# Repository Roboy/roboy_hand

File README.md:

Flashing with SWD via raspberry pi with openocd 

##  Default RPI-2 B settings
ip: 192.168.0.106

user: pi
pw: Roboy2016

##  access RPI
ssh pi@192.168.0.106

# working dir:
cd ~/Projekts/openocd/testing/samd21/

At91samd was programmed via openocd with an raspberry pi (https://iosoft.blog/2019/01/28/raspberry-pi-openocd/)

config file 

##  Pin header chestNut-PCB
1	VCC +3.3V
2	SWDIO
3	SWCLK
4	NC/
5	RESET
6	GND

##master config
source rpi2.cfg

transport select swd
adapter_khz 1000

set CHIPNAME at91samd21g18
source [find target/at91samdXX.cfg]

bindto 0.0.0.0

##raspberry config
# rpi2.cfg: OpenOCD interface on RPi v2+
echo "rpi2 cfg"
# Use RPi GPIO pins
interface bcm2835gpio

# Base address of I/O port
bcm2835gpio_peripheral_base 0x3F000000

# Clock scaling
bcm2835gpio_speed_coeffs 146203 36

# SWD                swclk swdio
# Header pin numbers 22    18
bcm2835gpio_swd_nums 25    24

# JTAG                tck tms tdi tdo
# Header pin numbers  22  18  16  15 
bcm2835gpio_jtag_nums 25  24  23  22

bcm2835gpio_srst_num 18
reset_config srst_only srst_push_pull

##rpi commands
###start openocd server
sudo openocd -f samd21_test.cfg
###telnet
telnet localhost 4444
###telnet commands
init
targets
reset halt
at91samd chip-erase
reset halt
at91samd bootloader 0
#program /home/pi/Projekts/openocd/testing/samd21/samd21_mkr1000.bin verify
#program /home/pi/Projekts/openocd/testing/samd21/samd21_sam_ba.bin verify
#program /home/pi/Projekts/openocd/testing/samd21/zero/samd21_sam_ba.bin verify
program /home/pi/Projekts/openocd/testing/samd21/samd21_genu_mkr1000.bin verify

at91samd bootloader 8192
reset
shutdown

#then mk1000 can be seltected in arduino after init flash the board will apear as "arduino zero"

Arduino head changes
Changed Pins.ino for finger.h file 

finger[0].attach(10, 11, A1, A9, false); // attach the thumb
finger[3].attach(4, 3, A0, 1, false); // attach the ring & pinky (fingers are inverted)
finger[1].attach(9, 6, A3, 0, false); // attach the index (finger is inverted)
finger[2].attach(5, 12, A2, A5, false); //doesn't move (could be wronge pin

#dump deltet ...... :
interface cmsis-dap
transport select swd
#Target
set CHIPNAME at91samd21e18
source [find target/at91samdXX2.cfg]
#source [find target/stm32f1x.cfg]

init
targets
reset halt
at91samd chip-erase
reset halt
at91samd bootloader 0
program D:/projects/SAMD_Loader/Firmware/all.bin verify
at91samd bootloader 8192
reset
shutdown

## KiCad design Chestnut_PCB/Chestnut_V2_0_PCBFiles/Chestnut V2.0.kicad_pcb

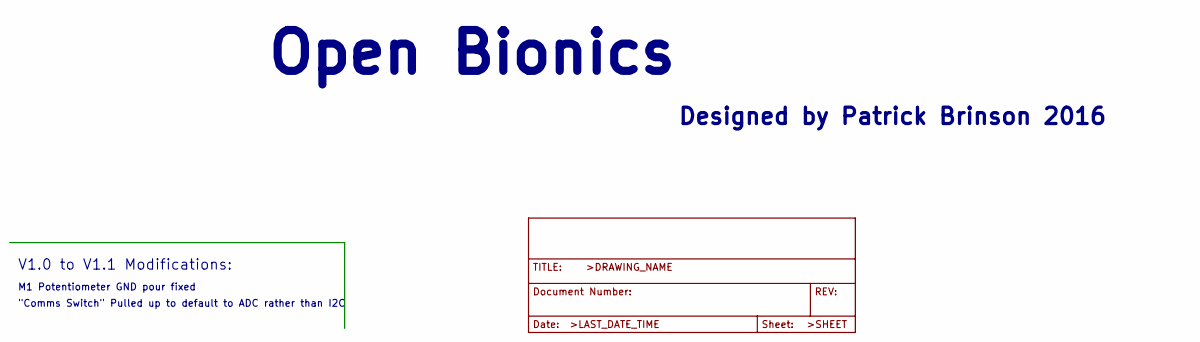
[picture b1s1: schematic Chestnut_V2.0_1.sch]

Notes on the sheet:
Open Bionics
Designed by Patrick Brinson 2016
V1.0 to V1.1 Modifications:
M1 Potentiometer GND pour fixed
"Comms Switch" Pulled up to default to ADC rather than I2C

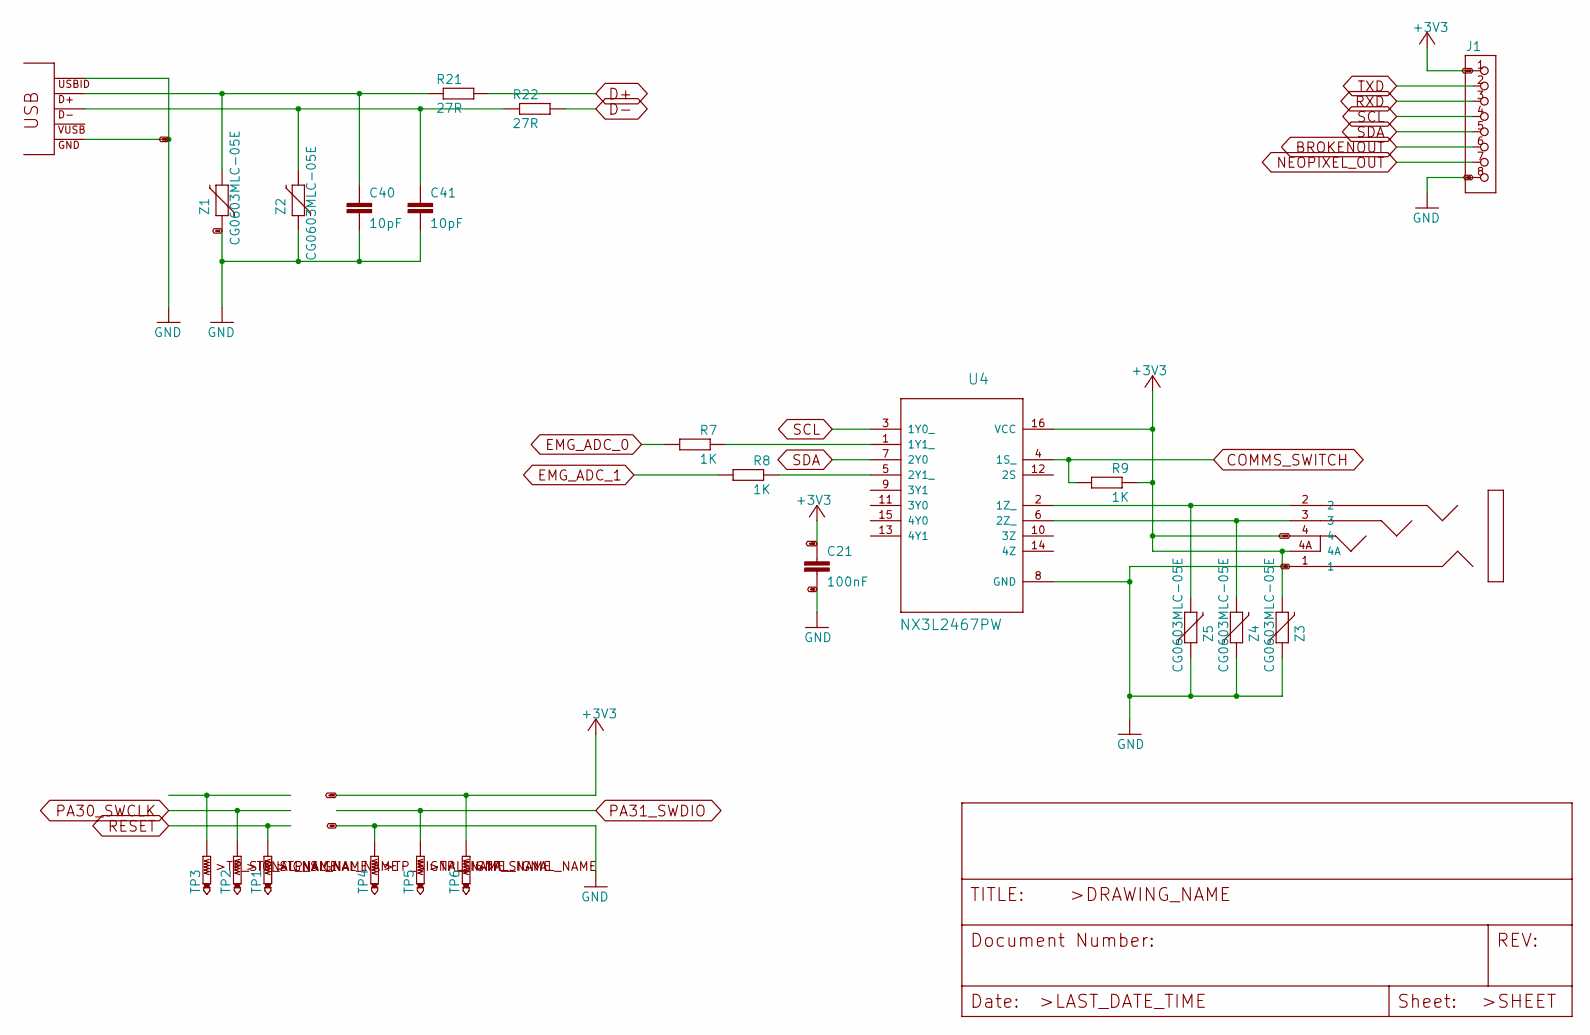
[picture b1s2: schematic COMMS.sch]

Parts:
C21: 100nF; C0402
C40, C41: 10pF; C0402
J1: CON_HEADER_1X08-PTH; M1X8
R7, R8, R9: 1K; R0402
R21, R22: 27R; R0402
TP1, TP2, TP3, TP4, TP5, TP6: PTR1TP11R; TP11R
U4: NX3L2467PW; SOP65P640X110-16N
U$7: LUMBERG_1503-13-VP3
USB1: CON-USB-F-MICRO-B; CONN_USB_MICRO-B
Z1, Z2, Z3, Z4, Z5: CG0603MLC-05E; CT_CN0603

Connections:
+3V3: C21.1, J1.1, R9.1, TP6.TP, U4.16 (VCC), U$7.4, U$7.4A, Z3.2; also elsewhere on the board
BROKENOUT: J1.6; also elsewhere on the board
COMMS_SWITCH: R9.2, U4.4 (1S_); also elsewhere on the board
D+: R21.2; also elsewhere on the board
D-: R22.2; also elsewhere on the board
EMG_ADC_0: R7.2; also elsewhere on the board
EMG_ADC_1: R8.2; also elsewhere on the board
GND: C21.2, C40.2, C41.2, J1.8, TP4.TP, U4.8 (GND), U$7.1, USB1.P4 (USBID), USB1.P5 (GND), Z1.1, Z2.1, Z3.1, Z4.1, Z5.1; also elsewhere on the board
NEOPIXEL_OUT: J1.7; also elsewhere on the board
unnamed: C40.1, R21.1, USB1.P3 (D+), Z1.2
unnamed: C41.1, R22.1, USB1.P2 (D-), Z2.2
unnamed: R7.1, U4.1 (1Y1_)
unnamed: R8.1, U4.5 (2Y1_)
unnamed: U4.2 (1Z_), U$7.2, Z5.2
unnamed: U4.6 (2Z_), U$7.3, Z4.2
PA30_SWCLK: TP2.TP; also elsewhere on the board
PA31_SWDIO: TP5.TP; also elsewhere on the board
RESET: TP1.TP; also elsewhere on the board
RXD: J1.3; also elsewhere on the board
SCL: J1.4, U4.3 (1Y0_); also elsewhere on the board
SDA: J1.5, U4.7 (2Y0); also elsewhere on the board
TXD: J1.2; also elsewhere on the board

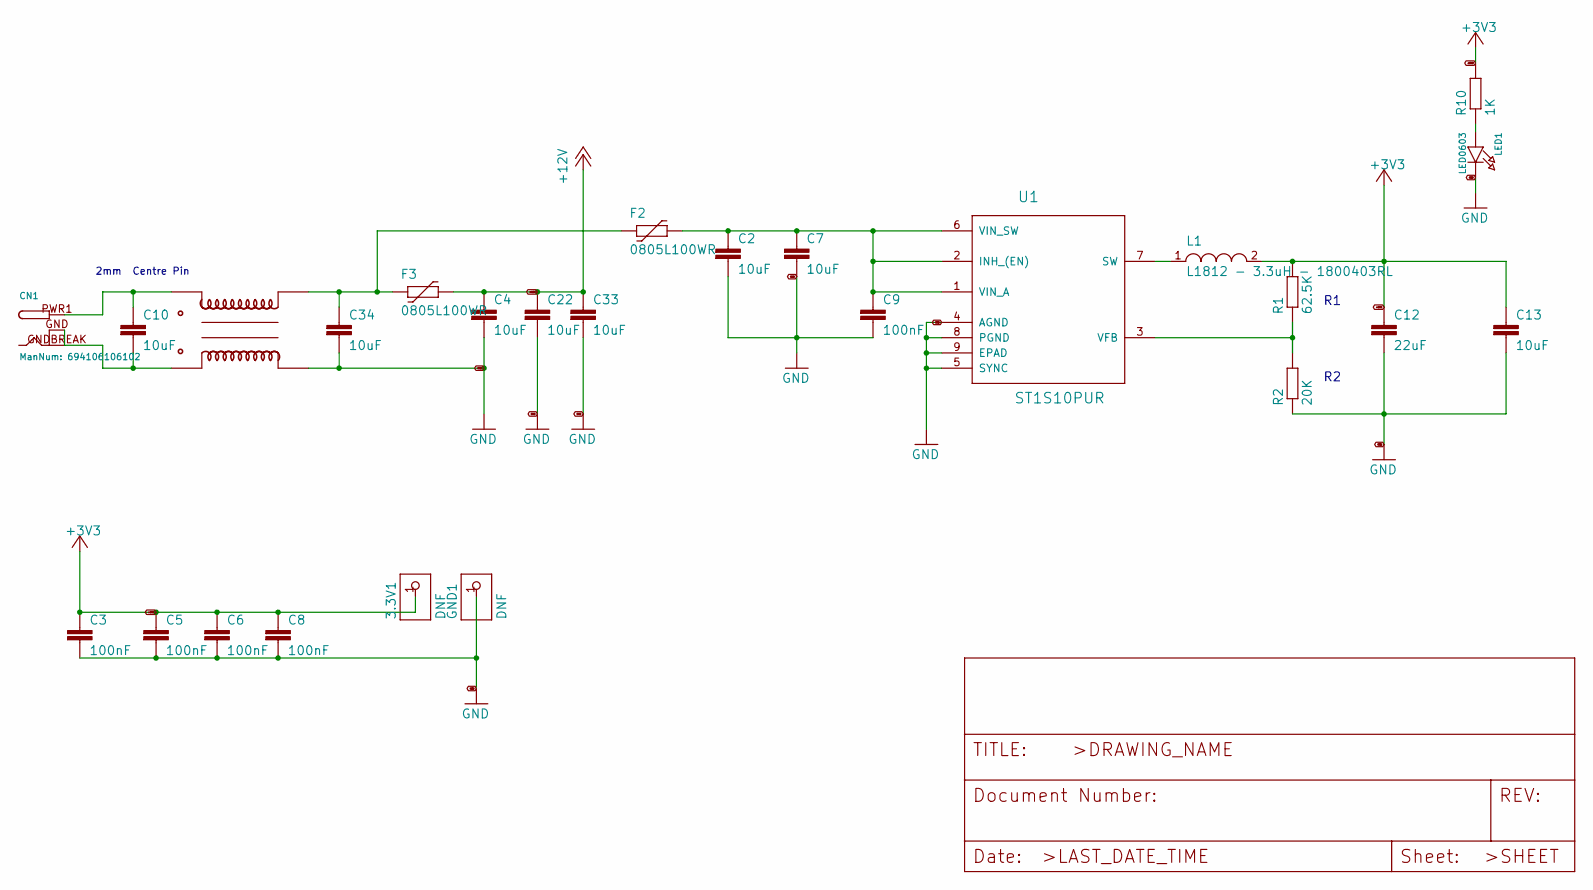
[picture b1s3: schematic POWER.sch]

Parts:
3.3V: DNF; 1X01_ROUND
C2, C4, C7, C10, C13, C22, C33, C34: 10uF; C0805
C3, C5, C6, C8, C9: 100nF; C0402
C12: 22uF; C1210
CN1: ManNum: 694106106102; DCJACK_2MM_SMT
F2, F3: 0805L100WR; PTC0805
GND: DNF; 1X01_ROUND
L1: L1812 - 3.3uH - 1800403RL; L1812
LED1: LED0603; CHIPLED_0603
R1: 62.5K; R0603
R2: 20K; R0603
R10: 1K; R0402
U1: ST1S10PUR; DFN400X400X100-9N
U$5: DLW5BTN501SQ2L

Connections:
+3V3: C3.1, C5.1, C6.1, C8.1, C12.1, C13.1, L1.2, R1.2, R10.2; also elsewhere on the board
+12V: C4.1, C22.1, C33.1, F3.2; also elsewhere on the board
GND: C2.2, C3.2, C4.2, C5.2, C6.2, C7.2, C8.2, C9.2, C12.2, C13.2, C22.2, C33.2, C34.2, LED1.C, R2.1, U1.4 (AGND), U1.5 (SYNC), U1.8 (PGND), U1.9 (EPAD), U$5.4; also elsewhere on the board
unnamed: C2.1, C7.1, C9.1, F2.2, U1.1 (VIN_A), U1.2 (INH_(EN)), U1.6 (VIN_SW)
unnamed: C10.1, CN1.PWR1 (PWR), U$5.1
unnamed: C10.2, CN1.GND (GNDBREAK), CN1.GNDBREAK (GND), U$5.3
unnamed: C34.1, F2.1, F3.1, U$5.2
unnamed: L1.1, U1.7 (SW)
unnamed: LED1.A, R10.1
unnamed: R1.1, R2.2, U1.3 (VFB)

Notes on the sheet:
2mm Centre Pin

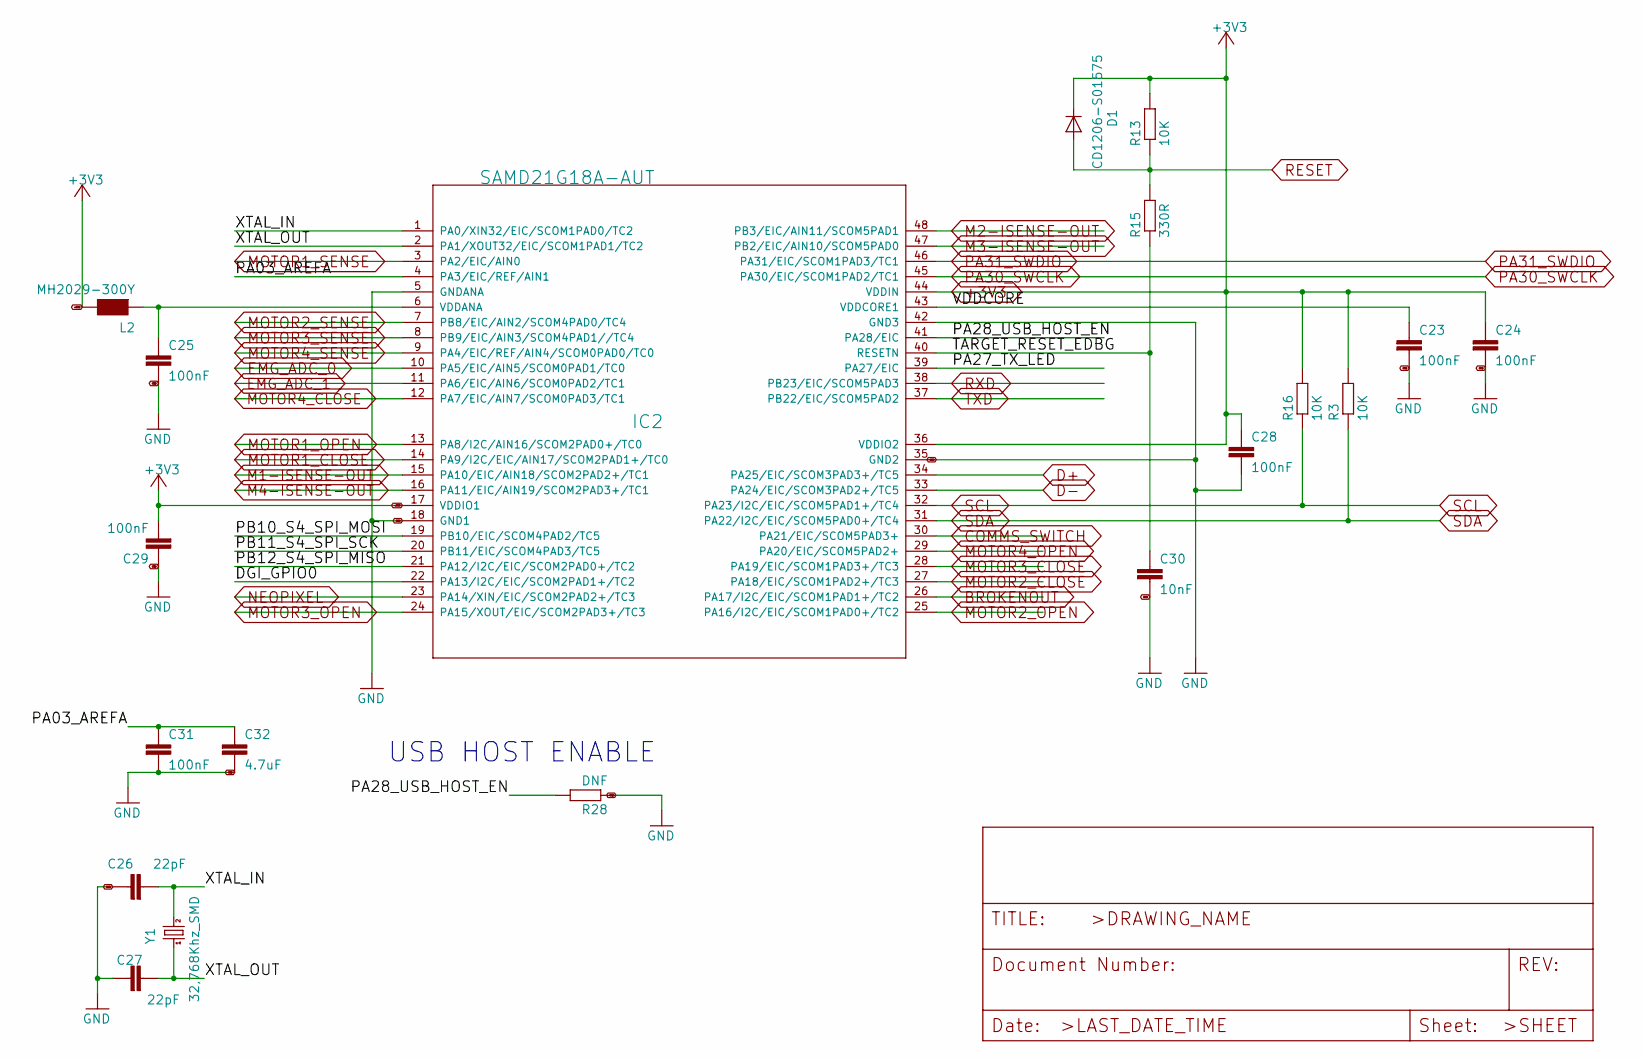
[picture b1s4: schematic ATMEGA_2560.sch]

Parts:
C23, C24, C25, C28, C29, C31: 100nF; C0402
C26, C27: 22pF; C0402
C30: 10nF; C0402
C32: 4.7uF; C0603
D1: CD1206-S01575; MINIMELF
IC2: SAMD21G18A-AUT; INTEGRATEDCIRCUITS_TQFP48-7X7
L2: MH2029-300Y; 0805
R3, R13, R16: 10K; R0402
R15: 330R; R0402
R28: DNF; R0402
Y1: 32,768Khz_SMD; RESONATOR_EPSON_FC_145

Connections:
+3V3: C24.1, C28.1, C29.2, D1.C, IC2.17 (VDDIO1), IC2.36 (VDDIO2), IC2.44 (VDDIN), L2.2, R3.2, R13.2, R16.2; also elsewhere on the board
/ATMEGA 2560/DGI_GPIO0: IC2.22 (PA13/I2C/EIC/SCOM2PAD1+/TC2)
/ATMEGA 2560/PA03_AREFA: C31.1, C32.1, IC2.4 (PA3/EIC/REF/AIN1)
/ATMEGA 2560/PA27_TX_LED: IC2.39 (PA27/EIC)
/ATMEGA 2560/PA28_USB_HOST_EN: IC2.41 (PA28/EIC), R28.2
/ATMEGA 2560/PB10_S4_SPI_MOSI: IC2.19 (PB10/EIC/SCOM4PAD2/TC5)
/ATMEGA 2560/PB11_S4_SPI_SCK: IC2.20 (PB11/EIC/SCOM4PAD3/TC5)
/ATMEGA 2560/PB12_S4_SPI_MISO: IC2.21 (PA12/I2C/EIC/SCOM2PAD0+/TC2)
/ATMEGA 2560/TARGET_RESET_EDBG: C30.1, IC2.40 (RESETN), R15.1
/ATMEGA 2560/VDDCORE: C23.1, IC2.43 (VDDCORE1)
/ATMEGA 2560/XTAL_IN: C26.2, IC2.1 (PA0/XIN32/EIC/SCOM1PAD0/TC2), Y1.P$2 (2)
/ATMEGA 2560/XTAL_OUT: C27.2, IC2.2 (PA1/XOUT32/EIC/SCOM1PAD1/TC2), Y1.P$1 (1)
BROKENOUT: IC2.26 (PA17/I2C/EIC/SCOM1PAD1+/TC2); also elsewhere on the board
COMMS_SWITCH: IC2.30 (PA21/EIC/SCOM5PAD3+); also elsewhere on the board
D+: IC2.34 (PA25/EIC/SCOM3PAD3+/TC5); also elsewhere on the board
D-: IC2.33 (PA24/EIC/SCOM3PAD2+/TC5); also elsewhere on the board
EMG_ADC_0: IC2.10 (PA5/EIC/AIN5/SCOM0PAD1/TC0); also elsewhere on the board
EMG_ADC_1: IC2.11 (PA6/EIC/AIN6/SCOM0PAD2/TC1); also elsewhere on the board
GND: C23.2, C24.2, C25.2, C26.1, C27.1, C28.2, C29.1, C30.2, C31.2, C32.2, IC2.5 (GNDANA), IC2.18 (GND1), IC2.35 (GND2), IC2.42 (GND3), R28.1; also elsewhere on the board
M1-ISENSE-OUT: IC2.15 (PA10/EIC/AIN18/SCOM2PAD2+/TC1); also elsewhere on the board
M2-ISENSE-OUT: IC2.48 (PB3/EIC/AIN11/SCOM5PAD1); also elsewhere on the board
M3-ISENSE-OUT: IC2.47 (PB2/EIC/AIN10/SCOM5PAD0); also elsewhere on the board
M4-ISENSE-OUT: IC2.16 (PA11/EIC/AIN19/SCOM2PAD3+/TC1); also elsewhere on the board
MOTOR1_CLOSE: IC2.14 (PA9/I2C/EIC/AIN17/SCOM2PAD1+/TC0); also elsewhere on the board
MOTOR1_OPEN: IC2.13 (PA8/I2C/AIN16/SCOM2PAD0+/TC0); also elsewhere on the board
MOTOR1_SENSE: IC2.3 (PA2/EIC/AIN0); also elsewhere on the board
MOTOR2_CLOSE: IC2.27 (PA18/EIC/SCOM1PAD2+/TC3); also elsewhere on the board
MOTOR2_OPEN: IC2.25 (PA16/I2C/EIC/SCOM1PAD0+/TC2); also elsewhere on the board
MOTOR2_SENSE: IC2.7 (PB8/EIC/AIN2/SCOM4PAD0/TC4); also elsewhere on the board
MOTOR3_CLOSE: IC2.28 (PA19/EIC/SCOM1PAD3+/TC3); also elsewhere on the board
MOTOR3_OPEN: IC2.24 (PA15/XOUT/EIC/SCOM2PAD3+/TC3); also elsewhere on the board
MOTOR3_SENSE: IC2.8 (PB9/EIC/AIN3/SCOM4PAD1//TC4); also elsewhere on the board
MOTOR4_CLOSE: IC2.12 (PA7/EIC/AIN7/SCOM0PAD3/TC1); also elsewhere on the board
MOTOR4_OPEN: IC2.29 (PA20/EIC/SCOM5PAD2+); also elsewhere on the board
MOTOR4_SENSE: IC2.9 (PA4/EIC/REF/AIN4/SCOM0PAD0/TC0); also elsewhere on the board
NEOPIXEL: IC2.23 (PA14/XIN/EIC/SCOM2PAD2+/TC3); also elsewhere on the board
unnamed: C25.1, IC2.6 (VDDANA), L2.1
PA30_SWCLK: IC2.45 (PA30/EIC/SCOM1PAD2/TC1); also elsewhere on the board
PA31_SWDIO: IC2.46 (PA31/EIC/SCOM1PAD3/TC1); also elsewhere on the board
RESET: D1.A, R13.1, R15.2; also elsewhere on the board
RXD: IC2.38 (PB23/EIC/SCOM5PAD3); also elsewhere on the board
SCL: IC2.32 (PA23/I2C/EIC/SCOM5PAD1+/TC4), R16.1; also elsewhere on the board
SDA: IC2.31 (PA22/I2C/EIC/SCOM5PAD0+/TC4), R3.1; also elsewhere on the board
TXD: IC2.37 (PB22/EIC/SCOM5PAD2); also elsewhere on the board

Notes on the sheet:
USB HOST ENABLE

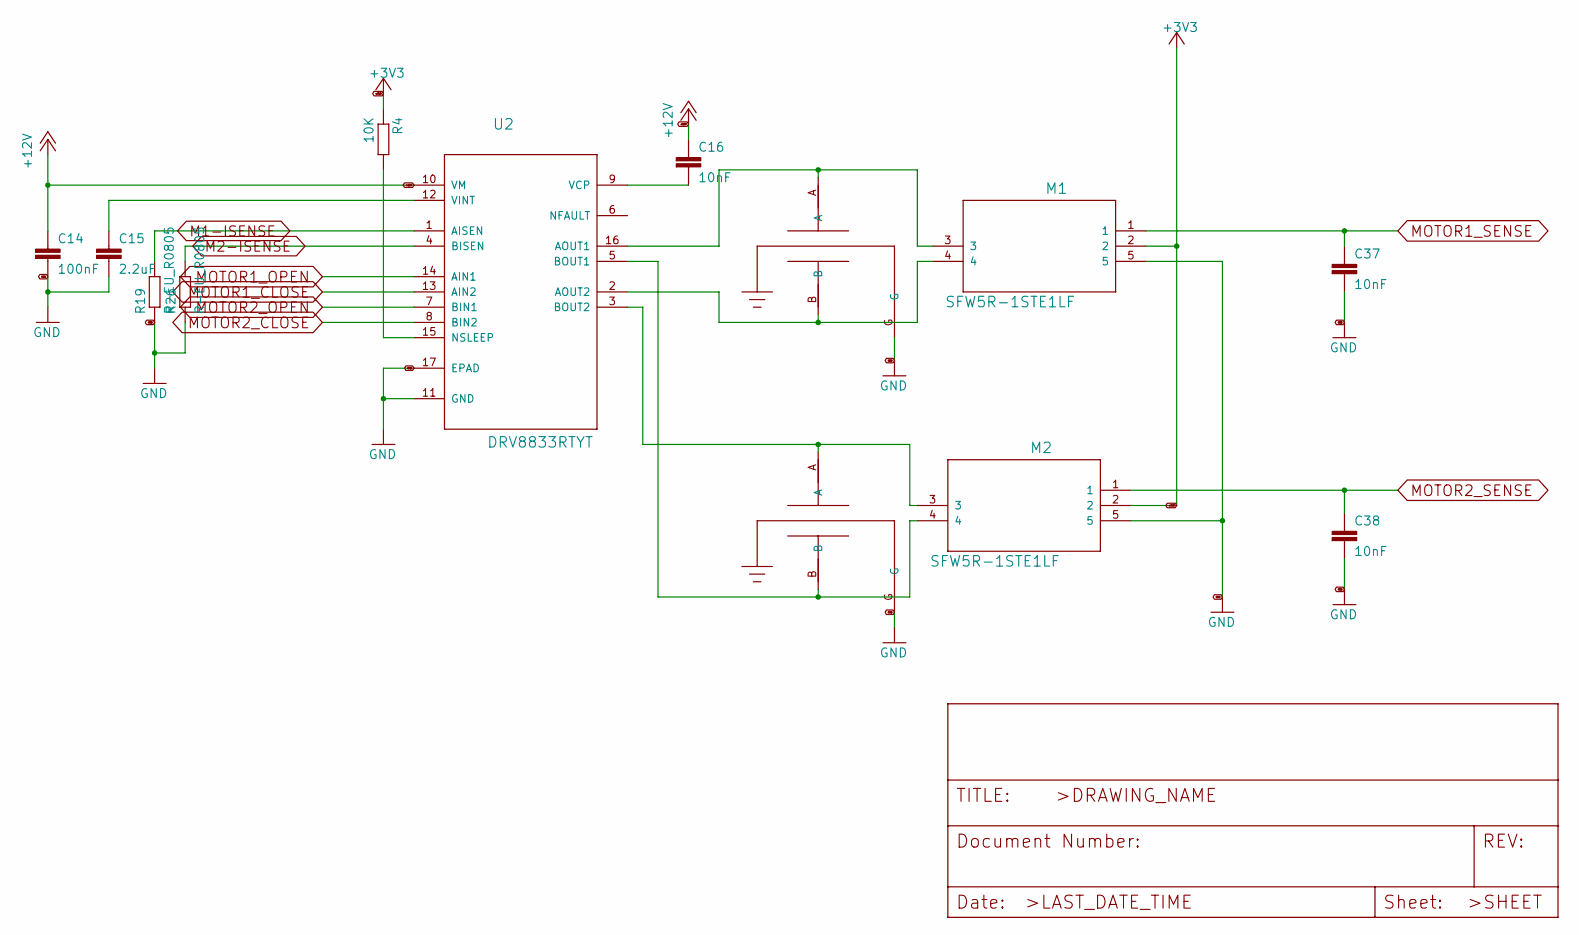
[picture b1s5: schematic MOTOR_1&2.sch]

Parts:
C14: 100nF; C0402
C15: 2.2uF; C0603
C16, C37, C38: 10nF; C0402
M1, M2: SFW5R-1STE1LF; FCI_SFW5R-1STE1LF
R4: 10K; R0402
R19, R26: R-EU_R0805; R0805
U2: DRV8833RTYT; QFN65P400X400X80-17N
U$8, U$19: 101X14N330MV4T_X2Y_0603

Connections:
+3V3: M1.2, M2.2, R4.1; also elsewhere on the board
+12V: C14.1, C16.1, U2.10 (VM); also elsewhere on the board
GND: C14.2, C15.2, C37.2, C38.2, M1.5, M2.5, R19.1, R26.1, U2.11 (GND), U2.17 (EPAD), U$8.G, U$19.G; also elsewhere on the board
M1-ISENSE: R19.2, U2.1 (AISEN); also elsewhere on the board
M2-ISENSE: R26.2, U2.4 (BISEN); also elsewhere on the board
MOTOR1_CLOSE: U2.13 (AIN2); also elsewhere on the board
MOTOR1_OPEN: U2.14 (AIN1); also elsewhere on the board
MOTOR1_SENSE: C37.1, M1.1; also elsewhere on the board
MOTOR2_CLOSE: U2.8 (BIN2); also elsewhere on the board
MOTOR2_OPEN: U2.7 (BIN1); also elsewhere on the board
MOTOR2_SENSE: C38.1, M2.1; also elsewhere on the board
unnamed: C15.1, U2.12 (VINT)
unnamed: C16.2, U2.9 (VCP)
unnamed: M1.3, U2.16 (AOUT1), U$19.A
unnamed: M1.4, U2.2 (AOUT2), U$19.B
unnamed: M2.3, U2.3 (BOUT2), U$8.A
unnamed: M2.4, U2.5 (BOUT1), U$8.B
unnamed: R4.2, U2.15 (NSLEEP)

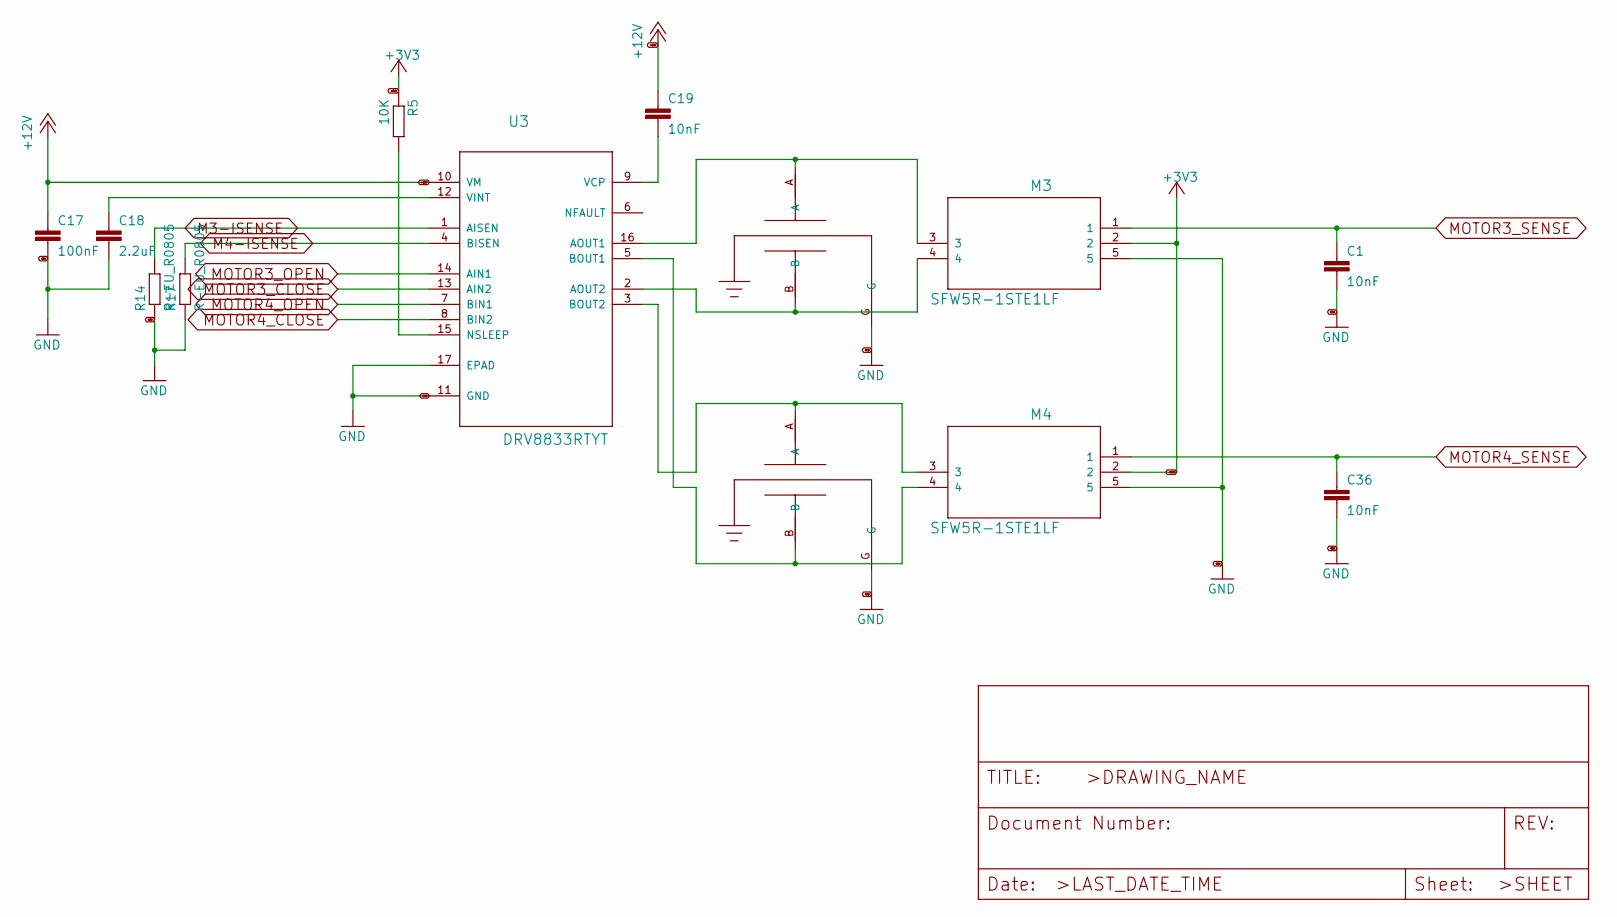
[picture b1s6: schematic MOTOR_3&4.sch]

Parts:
C1, C19, C36: 10nF; C0402
C17: 100nF; C0402
C18: 2.2uF; C0603
M3, M4: SFW5R-1STE1LF; FCI_SFW5R-1STE1LF
R5: 10K; R0402
R14, R17: R-EU_R0805; R0805
U3: DRV8833RTYT; QFN65P400X400X80-17N
U$9, U$10: 101X14N330MV4T_X2Y_0603

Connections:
+3V3: M3.2, M4.2, R5.1; also elsewhere on the board
+12V: C17.1, C19.1, U3.10 (VM); also elsewhere on the board
GND: C1.2, C17.2, C18.2, C36.2, M3.5, M4.5, R14.1, R17.1, U3.11 (GND), U3.17 (EPAD), U$9.G, U$10.G; also elsewhere on the board
M3-ISENSE: R14.2, U3.1 (AISEN); also elsewhere on the board
M4-ISENSE: R17.2, U3.4 (BISEN); also elsewhere on the board
MOTOR3_CLOSE: U3.13 (AIN2); also elsewhere on the board
MOTOR3_OPEN: U3.14 (AIN1); also elsewhere on the board
MOTOR3_SENSE: C1.1, M3.1; also elsewhere on the board
MOTOR4_CLOSE: U3.8 (BIN2); also elsewhere on the board
MOTOR4_OPEN: U3.7 (BIN1); also elsewhere on the board
MOTOR4_SENSE: C36.1, M4.1; also elsewhere on the board
unnamed: C18.1, U3.12 (VINT)
unnamed: C19.2, U3.9 (VCP)
unnamed: M3.3, U3.16 (AOUT1), U$9.A
unnamed: M3.4, U3.2 (AOUT2), U$9.B
unnamed: M4.3, U3.3 (BOUT2), U$10.A
unnamed: M4.4, U3.5 (BOUT1), U$10.B
unnamed: R5.2, U3.15 (NSLEEP)

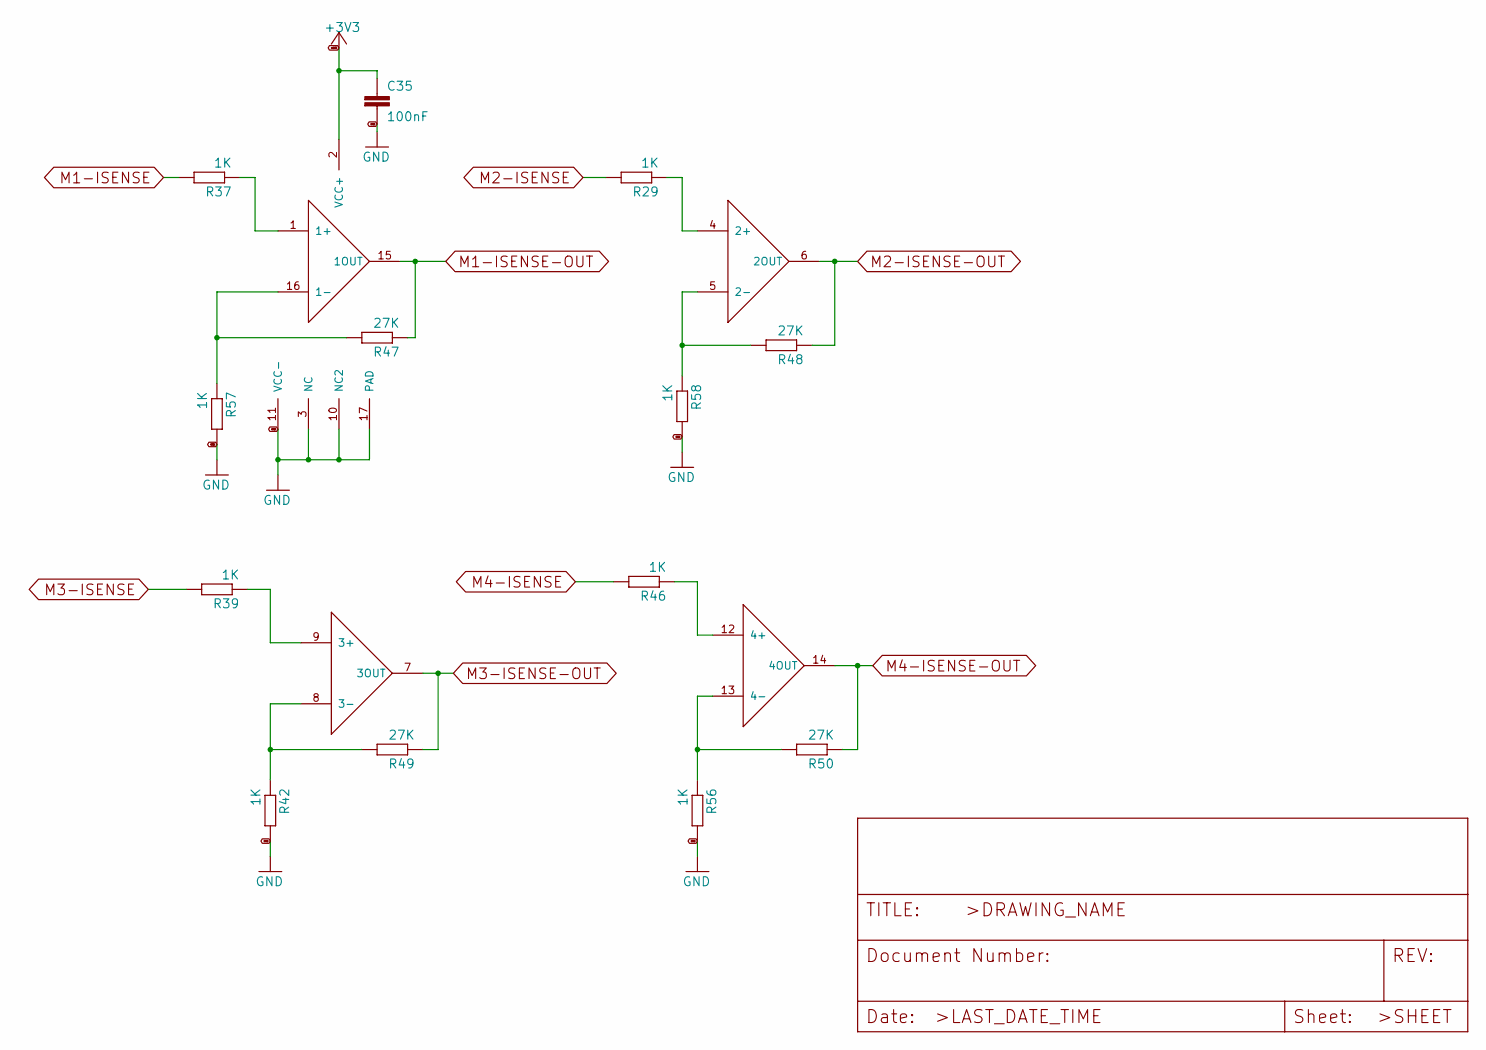
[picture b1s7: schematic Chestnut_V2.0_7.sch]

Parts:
C35: 100nF; C0402
R29, R37, R39, R42, R46, R56, R57, R58: 1K; R0402
R47, R48, R49, R50: 27K; R0402
U$15: TSZ124IQ4T

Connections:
+3V3: C35.1, U$15.2 (VCC+); also elsewhere on the board
GND: C35.2, R42.2, R56.2, R57.2, R58.2, U$15.3 (NC), U$15.10 (NC2), U$15.11 (VCC-), U$15.17 (PAD); also elsewhere on the board
M1-ISENSE: R37.2; also elsewhere on the board
M1-ISENSE-OUT: R47.1, U$15.15 (1OUT); also elsewhere on the board
M2-ISENSE: R29.2; also elsewhere on the board
M2-ISENSE-OUT: R48.1, U$15.6 (2OUT); also elsewhere on the board
M3-ISENSE: R39.2; also elsewhere on the board
M3-ISENSE-OUT: R49.1, U$15.7 (3OUT); also elsewhere on the board
M4-ISENSE: R46.2; also elsewhere on the board
M4-ISENSE-OUT: R50.1, U$15.14 (4OUT); also elsewhere on the board
unnamed: R29.1, U$15.4 (2+)
unnamed: R37.1, U$15.1 (1+)
unnamed: R39.1, U$15.9 (3+)
unnamed: R42.1, R49.2, U$15.8 (3-)
unnamed: R46.1, U$15.12 (4+)
unnamed: R47.2, R57.1, U$15.16 (1-)
unnamed: R48.2, R58.1, U$15.5 (2-)
unnamed: R50.2, R56.1, U$15.13 (4-)

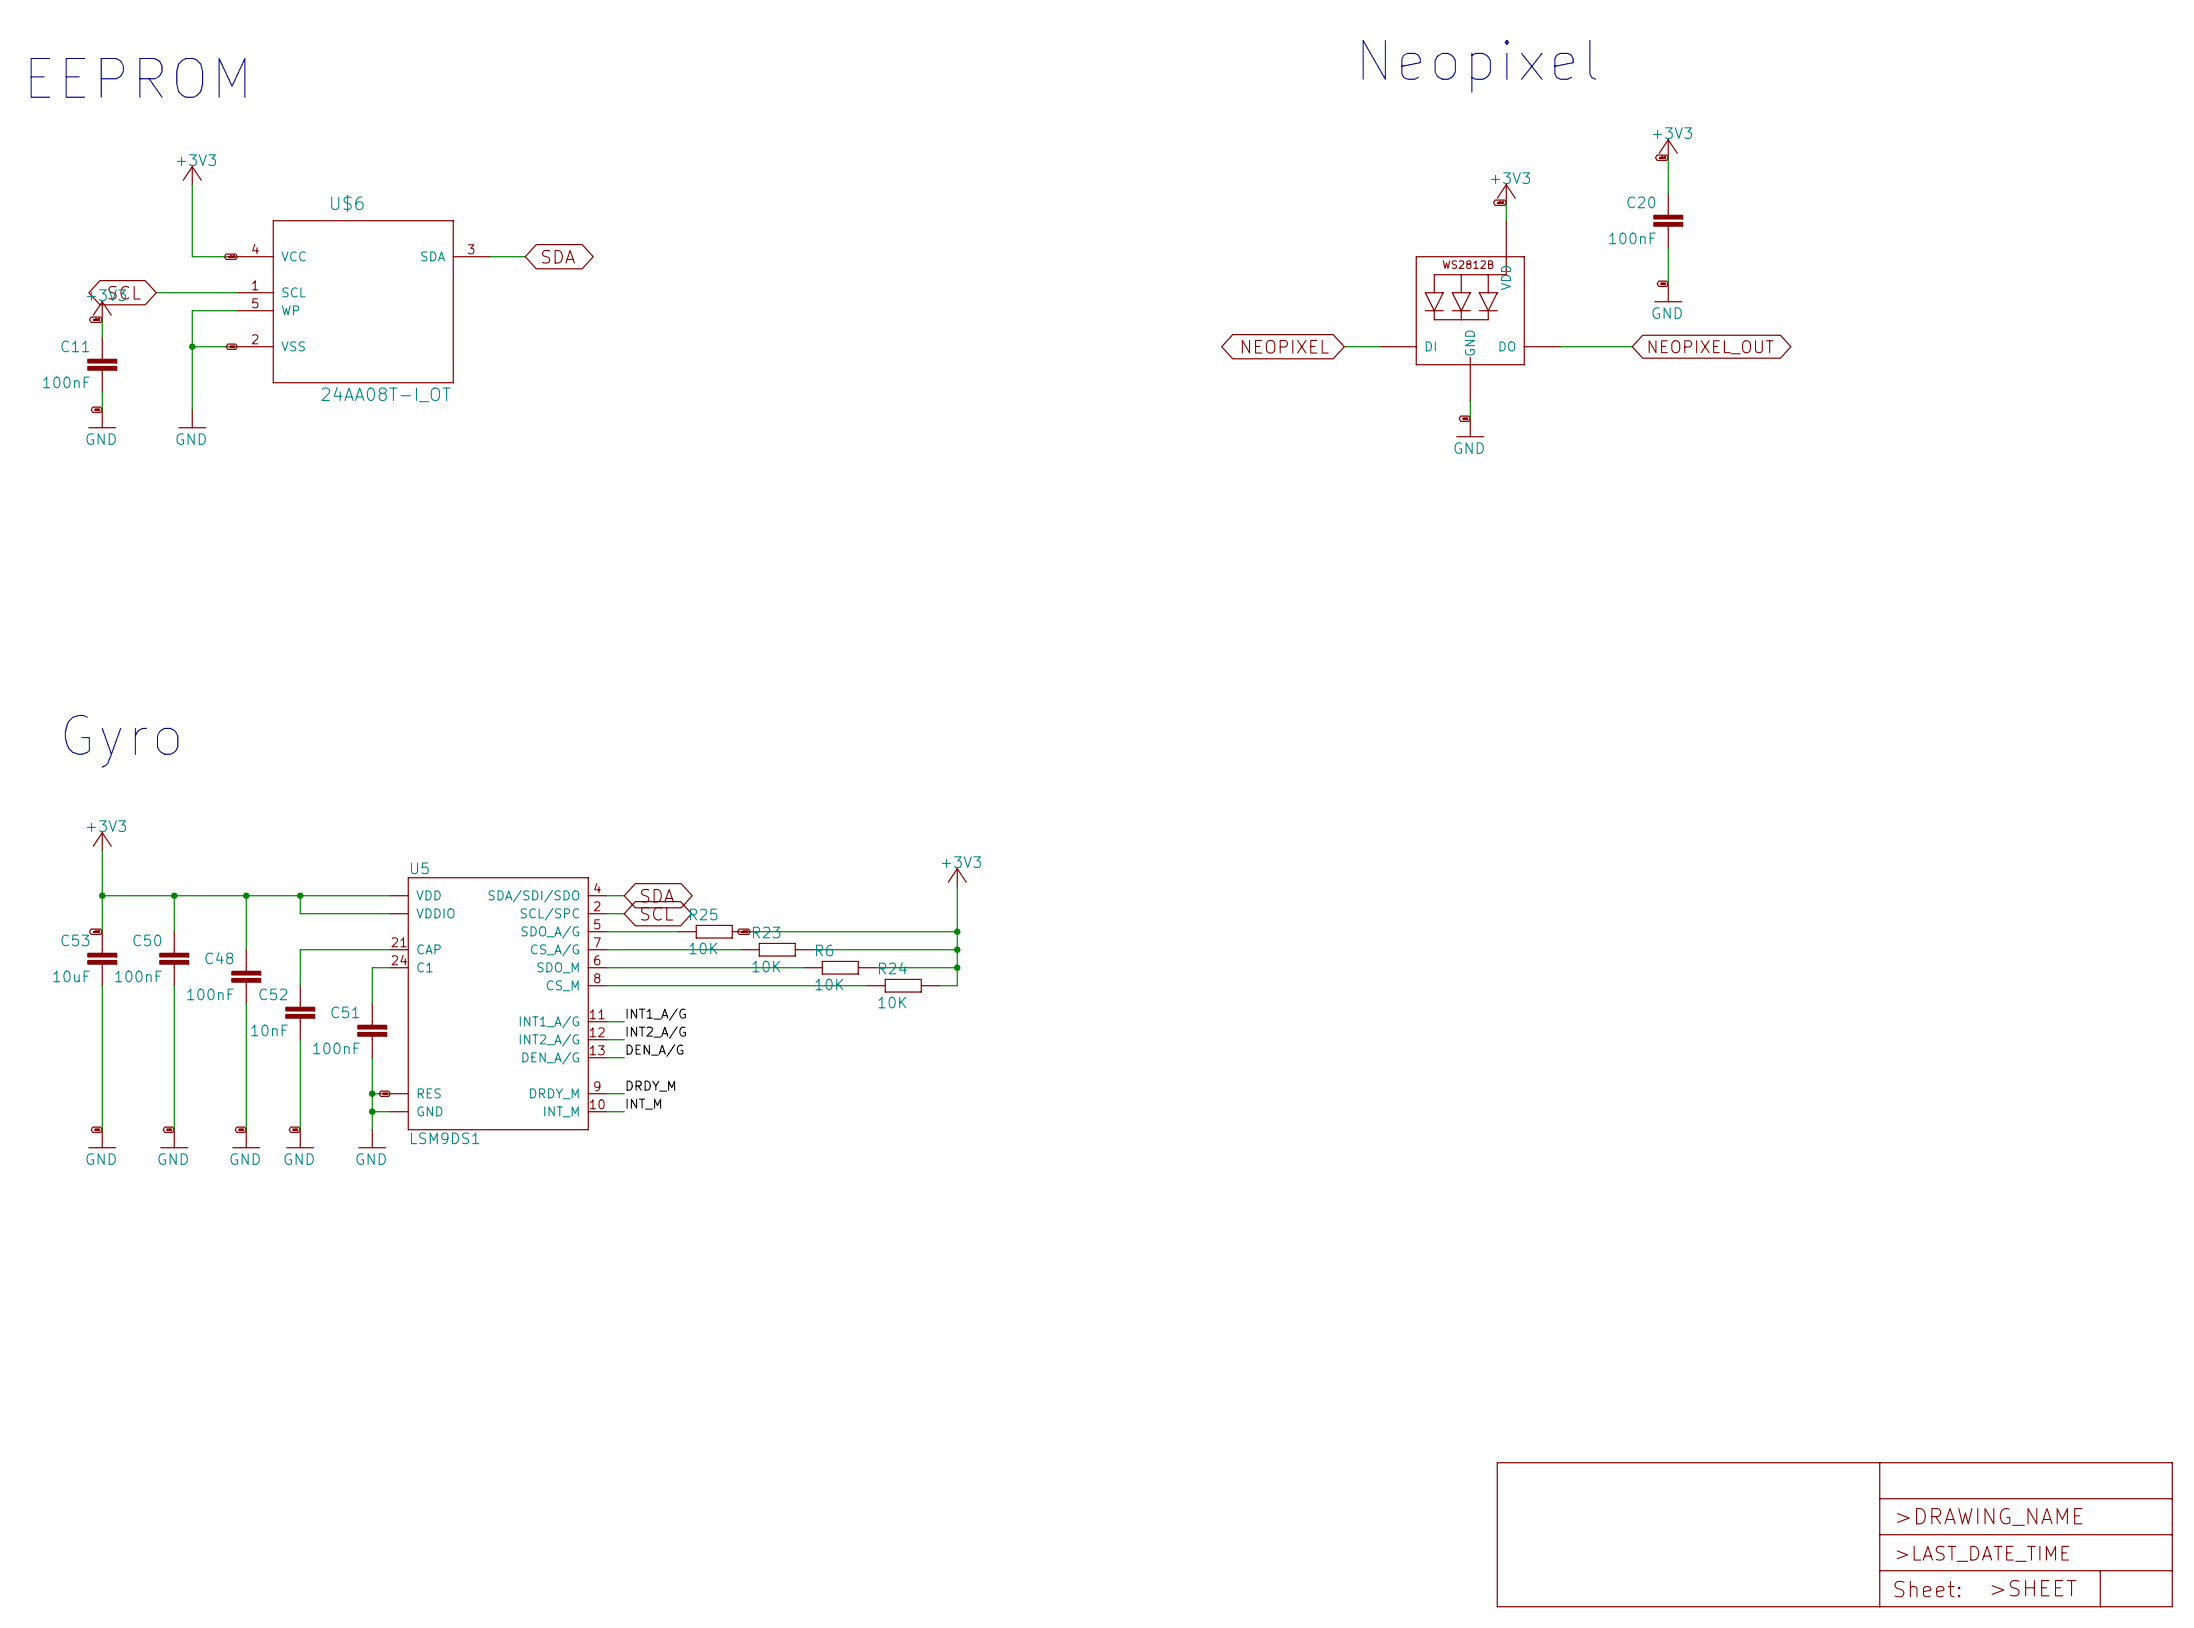
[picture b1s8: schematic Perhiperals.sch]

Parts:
C11, C20, C48, C50, C51: 100nF; C0402
C52: 10nF; C0402
C53: 10uF; C0805
LED2: WS2812B3535; LED3535
R6, R23, R24, R25: 10K; R0402
U5: LSM9DS1; LGA24-8X4
U$6: 24AA08T-I_OT; SOT95P290X145-5N

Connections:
+3V3: C11.1, C20.1, C48.1, C50.1, C53.1, LED2.2 (VDD), R6.2, R23.2, R24.2, R25.2, U5.1 (VDDIO), U5.3 (VDDIO), U5.22 (VDD), U5.23 (VDD), U$6.4 (VCC); also elsewhere on the board
/Perhiperals/DEN_A/G: U5.13 (DEN_A/G)
/Perhiperals/DRDY_M: U5.9 (DRDY_M)
/Perhiperals/INT1_A/G: U5.11 (INT1_A/G)
/Perhiperals/INT2_A/G: U5.12 (INT2_A/G)
/Perhiperals/INT_M: U5.10 (INT_M)
GND: C11.2, C20.2, C48.2, C50.2, C51.2, C52.2, C53.2, LED2.4 (GND), U5.14 (RES), U5.15 (RES), U5.16 (RES), U5.17 (RES), U5.18 (RES), U5.19 (GND), U5.20 (GND), U$6.2 (VSS), U$6.5 (WP); also elsewhere on the board
NEOPIXEL: LED2.1 (DI); also elsewhere on the board
NEOPIXEL_OUT: LED2.3 (DO); also elsewhere on the board
unnamed: C51.1, U5.24 (C1)
unnamed: C52.1, U5.21 (CAP)
unnamed: R6.1, U5.6 (SDO_M)
unnamed: R23.1, U5.7 (CS_A/G)
unnamed: R24.1, U5.8 (CS_M)
unnamed: R25.1, U5.5 (SDO_A/G)
SCL: U5.2 (SCL/SPC), U$6.1 (SCL); also elsewhere on the board
SDA: U5.4 (SDA/SDI/SDO), U$6.3 (SDA); also elsewhere on the board

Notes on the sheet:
EEPROM
Gyro
Neopixel

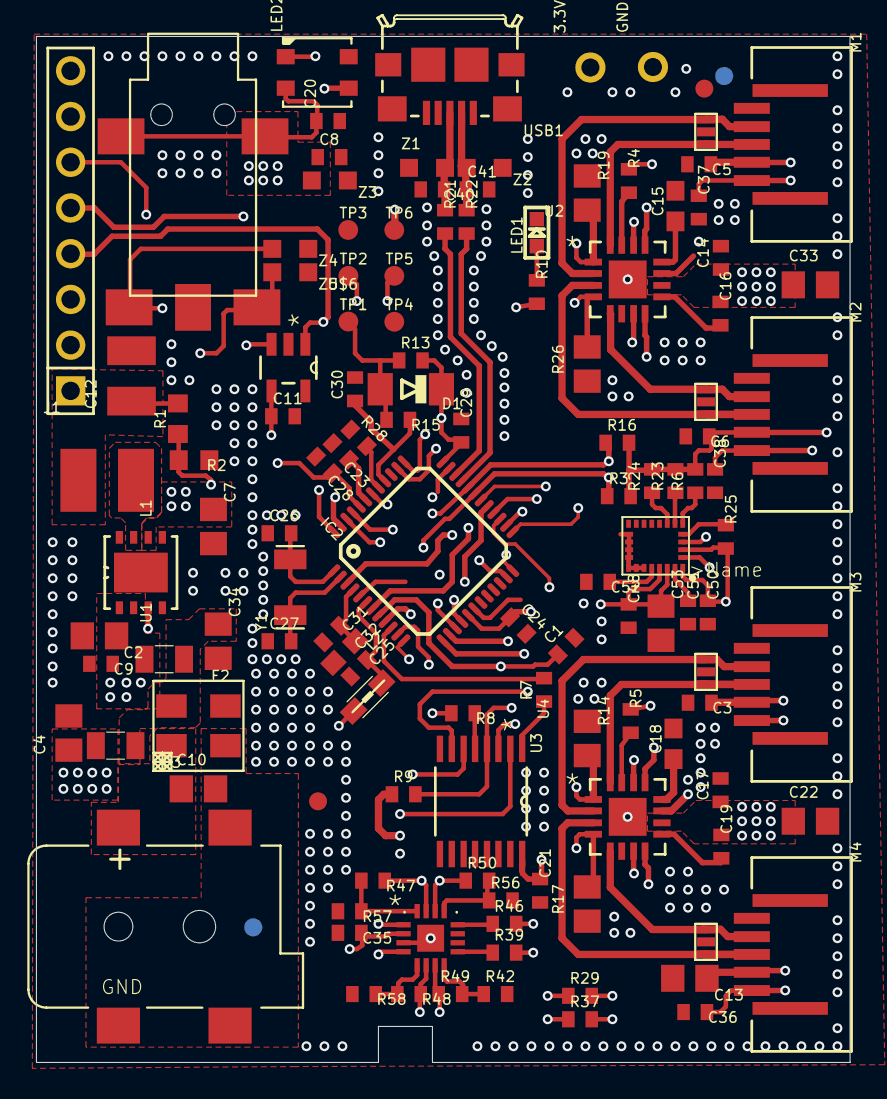
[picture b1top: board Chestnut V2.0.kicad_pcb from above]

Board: 4 copper layers, 45.2 x 57.0 mm, 126 parts (0 on the bottom side), 86 nets.

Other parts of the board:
3.3V1: DNF; 1X01_ROUND
GND1: DNF; 1X01_ROUND
U$1, U$2, U$3, U$4: FIDUCIAL_G10

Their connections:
+3V3: 3.3V1.1; also elsewhere on the board
GND: GND1.1; also elsewhere on the board

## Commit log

2020-01-28 init
2020-01-28 init commit
2020-01-28 added OB core samd
2020-01-28 added stuff
2020-01-28 added custom brunel code
2020-01-30 added new features
2020-03-13 added PCB
2020-03-13 additional hand messages draft
2020-03-13 need to limit the readouts to actual status requests
2020-03-13 pain in the ass
2020-03-16 freertos icebus frame matcher working
2020-03-16 with status response
2020-03-16 100Hz
2020-03-16 19200 baudrate seems to be the limit
2020-03-19 faster
2020-03-20 with controlmode
2020-03-20 screw samd
2020-04-20 with driveenable
2020-04-27 open close hand onboot
2020-05-04 with hand command counter
2020-08-20 with left hand correct finger assignement
